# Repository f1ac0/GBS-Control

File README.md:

# GBS-control
GBS-control, https://github.com/ramapcsx2/gbs-control, is an alternative firmware for Tvia Trueview5725 based upscalers / video converter boards such as the "GBS8200".

This repository contains the boards I designed to improve my own GBS-8200 with GBS-control using ESP12/ESP-M2 modules.

# Disclaimer
This is a hobbyist project, it comes with no warranty and no support.

This board is not endorsed by firmware author, please don't bother him with issues you might have because of it.

I publish my work under the CC-BY-NC-SA license.

If you find it useful and want to reward my hard work : I am always looking for Amiga/Amstrad CPC hardware to repair and hack, please contact me.

# BOM
- 1x ESP12 or ESP-M2 module
- 1x PLCC-44 through-hole socket
- 1x 10uF 0805 capacitor
- 2x 100nF 0805 capacitors (the one on EN might be omitted)
- 4x 10K 0805 resistors (the ones on GPIO0 and GPIO0 might be omitted)

# Making it
The socket must be prepared before soldering : remove the 4 small stands inside the socket and file plastic from its top up to the contacts so the socket can plug on top of the PLCC chip without popping out. Be careful to remove plastic debris, and check its orientation before soldering under the PCB.

Check for shorts at least between power traces before applying power !

The programming port does not need to be soldered since it needs to be programmed just once : you can just hold it in place during the few seconds required for programming with an USB to serial adapter. When you want to program it, remember to short GPIO0 to ground before applying power.

# Using it
Plug the GBS-control board on the PLCC controller. Connect the clock generator board on the clock port.

There is no need to populate P8 since it is shorted by the board. It also takes the 3.3V from the PLCC chip so no additional power connection is required.

See GBS-control wiki for software setup.

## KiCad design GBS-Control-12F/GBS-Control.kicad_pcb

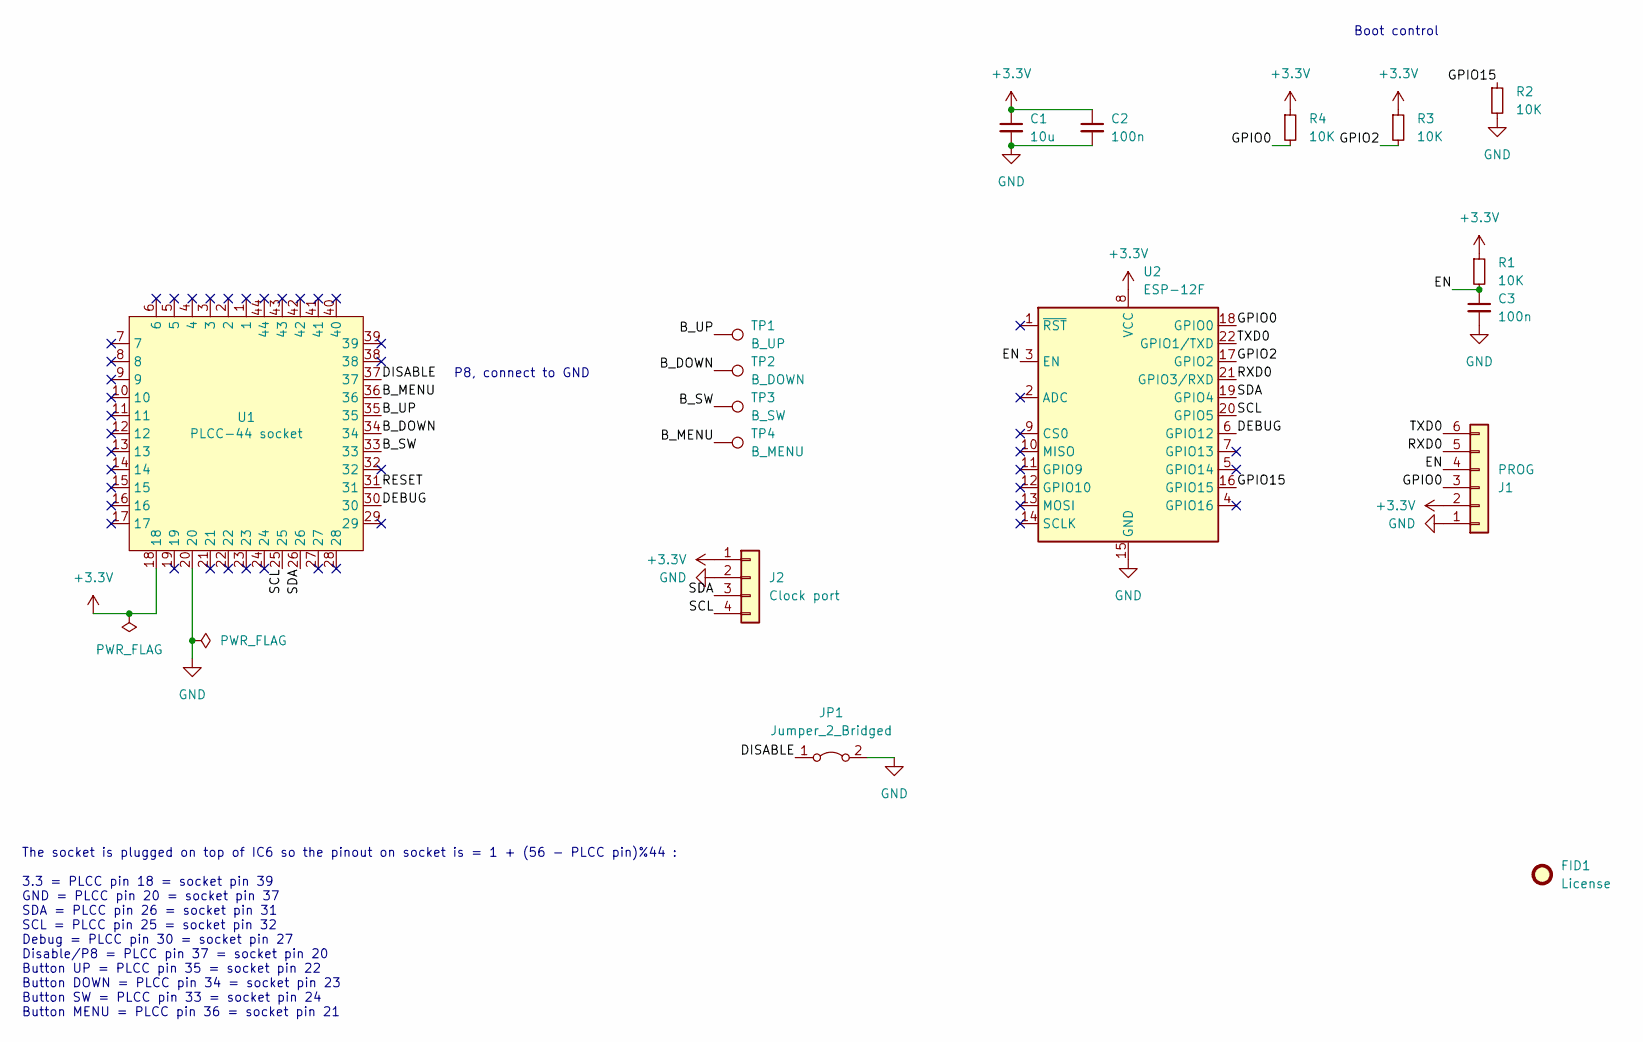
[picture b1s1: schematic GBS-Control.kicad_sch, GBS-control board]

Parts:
C1: 10u; C_0805_2012Metric
C2, C3: 100n; C_0805_2012Metric
FID1: License; CC_BY_NC_SA_long_silkscreen
J1: PROG; PinSocket_1x06_P2.54mm_Vertical
J2: Clock port; PinHeader_1x04_P2.54mm_Vertical
JP1: Jumper_2_Bridged; SolderJumper-2_P1.3mm_Bridged_RoundedPad1.0x1.5mm
R1, R2, R3, R4: 10K; R_0805_2012Metric
TP1: B_UP; TestPoint_Pad_D1.0mm
TP2: B_DOWN; TestPoint_Pad_D1.0mm
TP3: B_SW; TestPoint_Pad_D1.0mm
TP4: B_MENU; TestPoint_Pad_D1.0mm
U1: PLCC-44 socket; PLCC-44_THT-SocketOnTop
U2: ESP-12F; ESP-12E_No-bottom-pins

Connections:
+3.3V: C1.1, C2.1, J1.2, J2.1, R1.1, R3.1, R4.1, U1.18, U2.8 (VCC)
/B_DOWN: TP2.1, U1.34
/B_MENU: TP4.1, U1.36
/B_SW: TP3.1, U1.33
/B_UP: TP1.1, U1.35
/DEBUG: U1.30, U2.6 (GPIO12)
/DISABLE: JP1.1 (A), U1.37
/EN: C3.1, J1.4, R1.2, U2.3 (EN)
/GPIO0: J1.3, R4.2, U2.18 (GPIO0)
/GPIO2: R3.2, U2.17 (GPIO2)
/GPIO15: R2.1, U2.16 (GPIO15)
/RESET: U1.31
/RXD0: J1.5, U2.21 (GPIO3/RXD)
/SCL: J2.4, U1.25, U2.20 (GPIO5)
/SDA: J2.3, U1.26, U2.19 (GPIO4)
/TXD0: J1.6, U2.22 (GPIO1/TXD)
GND: C1.2, C2.2, C3.2, J1.1, J2.2, JP1.2 (B), R2.2, U1.20, U2.15 (GND)

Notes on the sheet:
Boot control
P8, connect to GND
The socket is plugged on top of IC6 so the pinout on socket is = 1 + (56 - PLCC pin)%44 : 3.3 = PLCC pin 18 = socket pin 39 GND = PLCC pin 20 = socket pin 37 SDA = PLCC pin 26 = socket pin 31 SCL = PLCC pin 25 = socket pin 32 Debug = PLCC pin 30 = socket pin 27 Disable/P8 = PLCC pin 37 = socket pin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

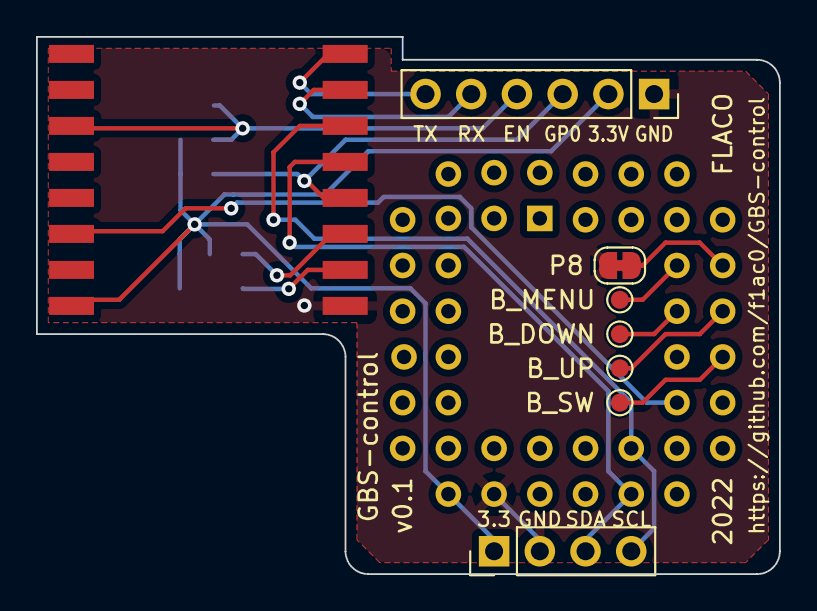
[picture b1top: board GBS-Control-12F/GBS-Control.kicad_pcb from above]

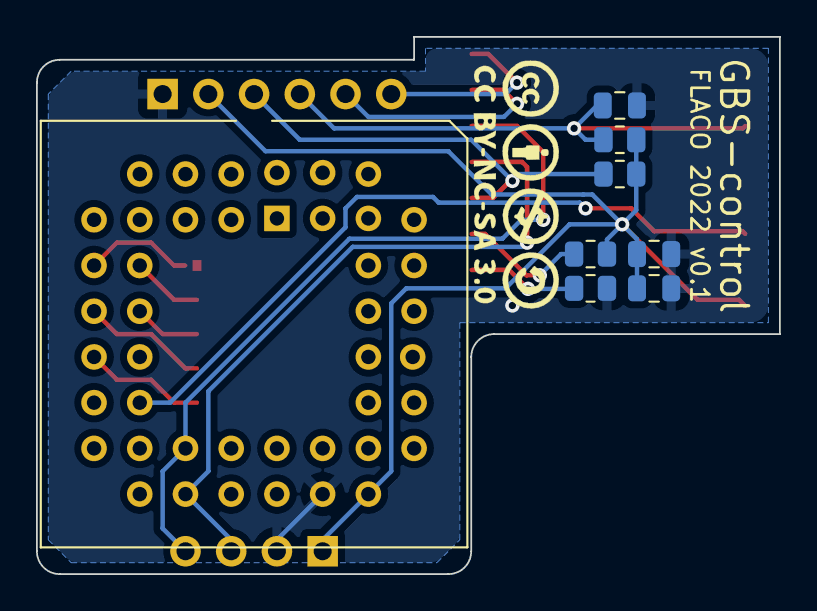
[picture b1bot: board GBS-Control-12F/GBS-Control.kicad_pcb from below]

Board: 2 copper layers, 41.3 x 29.8 mm, 17 parts (9 on the bottom side), 16 nets.

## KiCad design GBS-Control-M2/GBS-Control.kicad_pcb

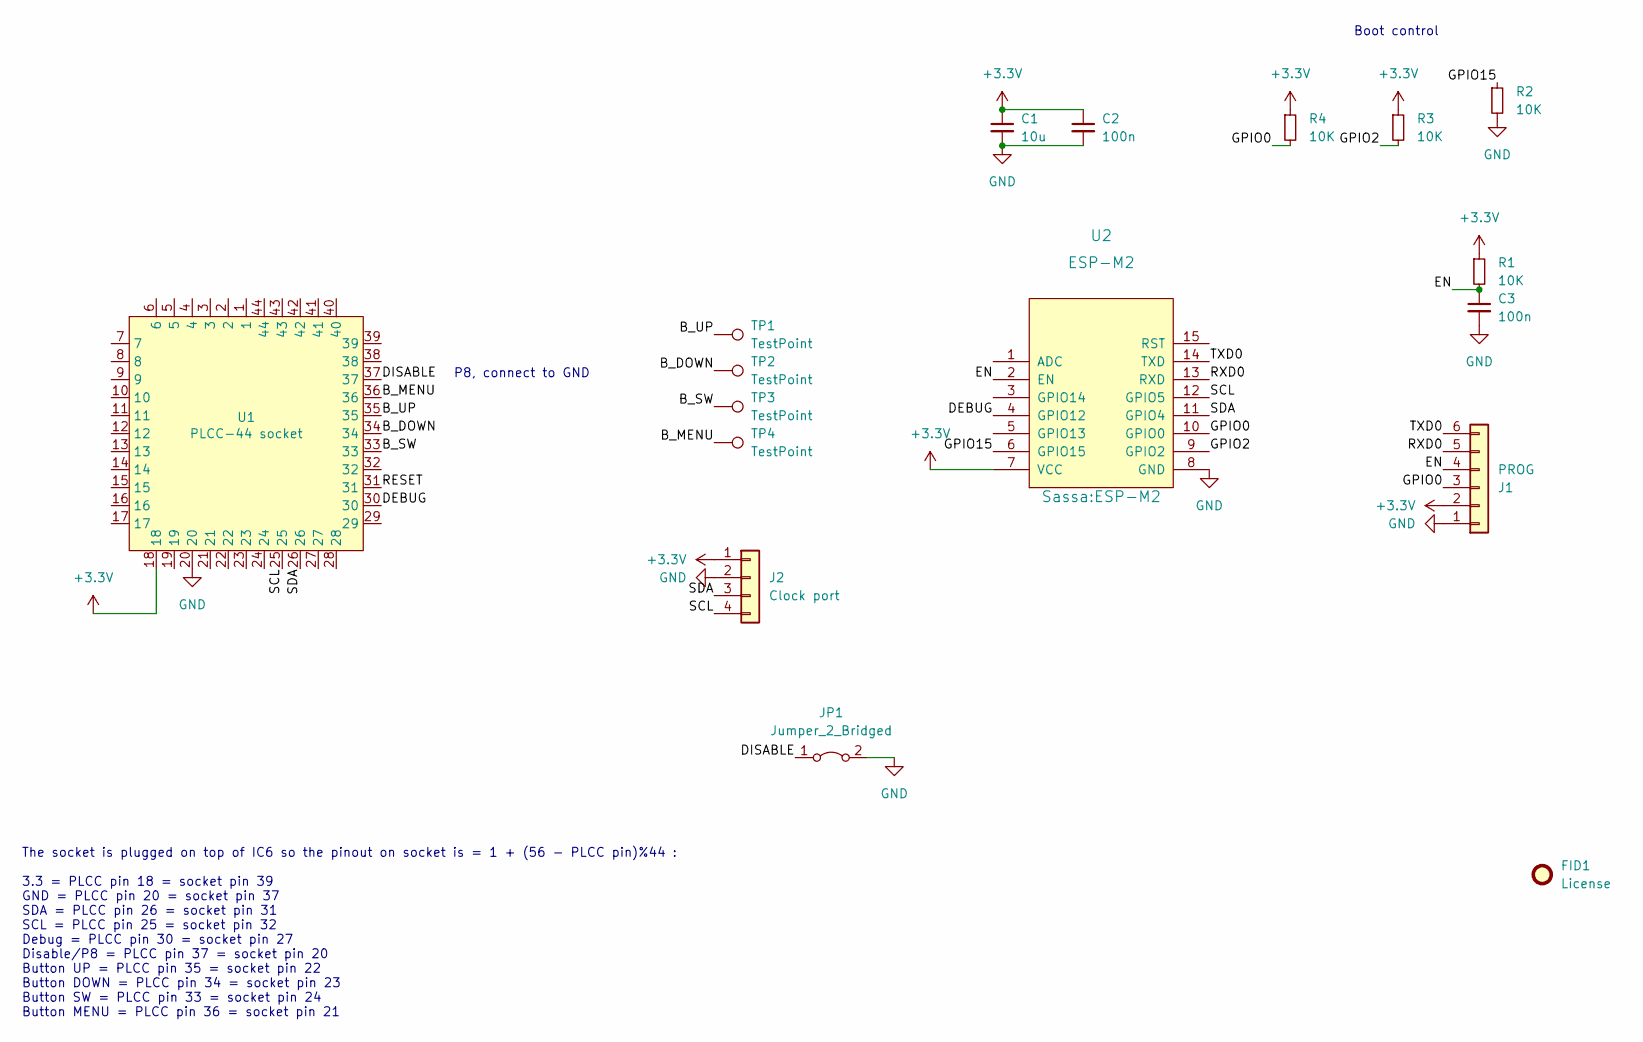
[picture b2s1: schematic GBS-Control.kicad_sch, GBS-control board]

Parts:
C1: 10u; C_0805_2012Metric
C2, C3: 100n; C_0805_2012Metric
FID1: License; CC_BY_NC_SA_square_silkscreen_4.8x4.8mm
J1: PROG; PinSocket_1x06_P2.54mm_Vertical
J2: Clock port; PinHeader_1x04_P2.54mm_Vertical
JP1: Jumper_2_Bridged; SolderJumper-2_P1.3mm_Bridged_RoundedPad1.0x1.5mm
R1, R2, R3, R4: 10K; R_0805_2012Metric
TP1, TP2, TP3, TP4: TestPoint; TestPoint_Pad_D1.0mm
U1: PLCC-44 socket; PLCC-44_THT-SocketOnTop
U2: ESP-M2

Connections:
+3.3V: C1.1, C2.1, J1.2, J2.1, R1.1, R3.1, R4.1, U1.18, U2.7 (VCC)
/B_DOWN: TP2.1, U1.34
/B_MENU: TP4.1, U1.36
/B_SW: TP3.1, U1.33
/B_UP: TP1.1, U1.35
/DEBUG: U1.30, U2.4 (GPIO12)
/DISABLE: JP1.1 (A), U1.37
/EN: C3.1, J1.4, R1.2, U2.2 (EN)
/GPIO0: J1.3, R4.2, U2.10 (GPIO0)
/GPIO2: R3.2, U2.9 (GPIO2)
/GPIO15: R2.1, U2.6 (GPIO15)
/RESET: U1.31
/RXD0: J1.5, U2.13 (RXD)
/SCL: J2.4, U1.25, U2.12 (GPIO5)
/SDA: J2.3, U1.26, U2.11 (GPIO4)
/TXD0: J1.6, U2.14 (TXD)
GND: C1.2, C2.2, C3.2, J1.1, J2.2, JP1.2 (B), R2.2, U1.20, U2.8 (GND)

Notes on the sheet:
Boot control
P8, connect to GND
The socket is plugged on top of IC6 so the pinout on socket is = 1 + (56 - PLCC pin)%44 : 3.3 = PLCC pin 18 = socket pin 39 GND = PLCC pin 20 = socket pin 37 SDA = PLCC pin 26 = socket pin 31 SCL = PLCC pin 25 = socket pin 32 Debug = PLCC pin 30 = socket pin 27 Disable/P8 = PLCC pin 37 = socket pin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

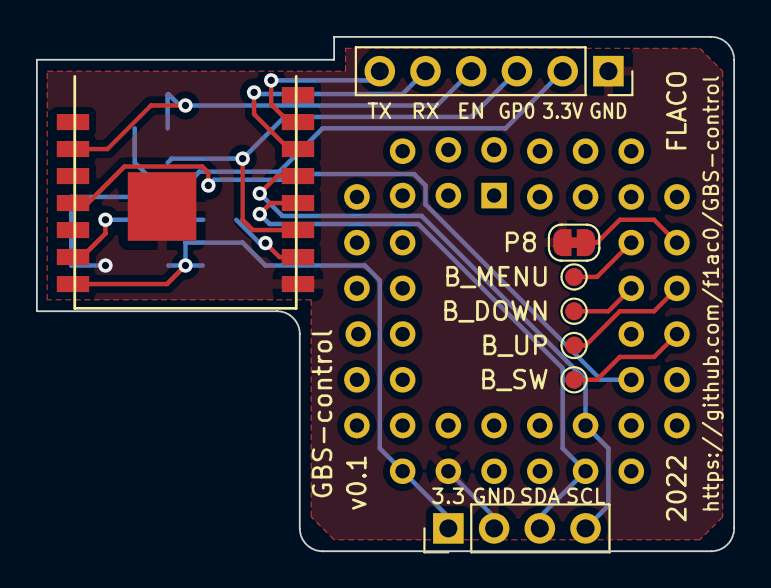
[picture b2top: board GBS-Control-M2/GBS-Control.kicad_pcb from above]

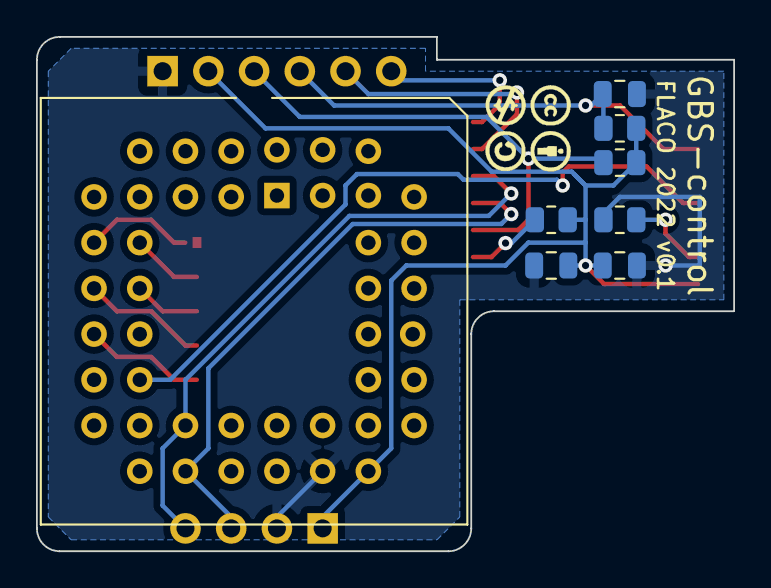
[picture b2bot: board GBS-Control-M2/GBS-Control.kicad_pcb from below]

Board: 2 copper layers, 38.7 x 28.6 mm, 17 parts (9 on the bottom side), 16 nets.

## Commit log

2022-10-23 Repository init with KiCAD boards, Readme and license
2022-10-25 KiCAD : add a port to connect the Si5351 Clock Generator
2022-11-23 GBS-Control-12F, GBS-Control-M2 : update socket symbol and footprint, no PCB change
2024-01-21 GBS-Control-12F, GBS-Control-M2 : update ibom ; small silkscreen change

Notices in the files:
GBS-Control-12F/GBS-Control.kicad_pcb:
FLACO 2022 CC-BY-NC-SA
GBS-Control-M2/GBS-Control.kicad_pcb:
FLACO 202 CC-BY-NC-SA
